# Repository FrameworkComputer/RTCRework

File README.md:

# RTC Rework

## Requesting an RTC Battery Substitute module

If you have an 11th Gen system or Mainboard, you can now [reach out to support](https://framework.kustomer.help/contact/support-request-ryon9uAuq) to request a free RTC Battery Substitute module. 
To make the request process go smoothly, enter the email address that you ordered the 11th Gen product on and/or include photos of the system and Mainboard serial numbers.

Note that there are no constraints making this request other than being an 11th Gen system or Mainboard owner (whether or not you are in warranty), with the exception of those from Mystery Boxes. 
We ask that you really make sure you are comfortable with performing soldering on expensive electronics items before performing the installation, 
as we won’t be able to provide advice or support around soldering or provide fixes for failed soldering attempts. 
We also ask that you only make the request if you’ve faced needing to perform a Mainboard reset, as we want to avoid waste.

## Details

This is a "fake" ML1220 RTC Battery that can be inserted into an 11th Gen Intel Core Framework Laptop Mainboard as a
replacement for a real ML1220.  There is a known issue on 11th Gen where RTC battery voltage dropping below a certain
level can in some scenarios result in the CPU entering a bad state and not booting until the main battery and RTC battery
are cycled.

With this fake RTC Battery, the RTC circuit remains powered from either AC or the main battery at all times,
preventing the CPU from entering the bad state.  Note that since it is not a real battery, if both AC and the main
battery are disconnected, the clock will be reset.  The OS will be able to recover the clock once it connects to a network.
This behavior matches essentially how 12th Gen works with the RTC battery removed, and how 13th Gen and Ryzen 7040 Series work
by default, since we no longer ship with an RTC battery installed.

## Fabrication
The outputs in the outputs directory contain the necessary information to have a fab house like PCBWay or similar fabricate
the PCBs and do SMT and manual assembly.  Note that the PCB must be 2.0mm thick, have ENIG plating, and have edge plating.

## Assembly
Steps 1 through 3 can be done by the PCB fab/assembly supplier (we've used PCBWay, but there are many similar ones), while
the remaining steps are done on the specific Framework Laptop.

1. Strip 3mm from each side of 60mm long, 30 AWG solid wire.
2. Solder one side of the wire to the pad on the top of the PCB that is labelled 17.6V
3. Apply a 10mm diameter disc of kapton tape on the top of the PCB, covering the pad and SMT parts
4. Follow the [step by step guide](https://guides.frame.work/Guide/RTC+Battery+Substitution+on+11th+Gen+Intel%C2%AE+Core%E2%84%A2/203) with photos and video for the remaining steps.

## License
RTC Rework © 2023 by Framework Computer Inc is licensed under CC BY 4.0. To view a copy of this license, visit http://creativecommons.org/licenses/by/4.0/

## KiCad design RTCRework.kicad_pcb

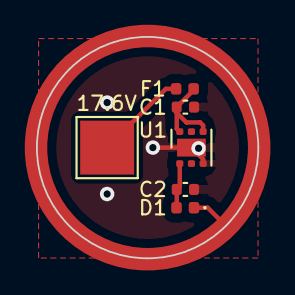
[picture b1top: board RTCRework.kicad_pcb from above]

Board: 2 copper layers, 12.3 x 12.3 mm, 7 parts (1 on the bottom side), 4 nets.

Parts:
C1, C2: 1uF; C_0402_1005Metric
D1: D_Schottky; D_0402_1005Metric
F1: Fuse; Fuse_0402_1005Metric
J1: Conn_01x01; TestPoint_Pad_3.0x3.0mm
J2: Conn_01x01; TestPoint_Pad_D4.0mm
U1: NCP718AMT330TBG; WSON-6-1EP_2x2mm_P0.65mm_EP1x1.6mm

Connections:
+17.6V: F1.1, J1.1
GND: C1.2, C2.2, J2.1, U1.3 (GND), U1.7 (GND)
unnamed: C2.1, D1.2 (A), U1.1 (OUT)
unnamed: C1.1, F1.2, U1.4 (EN), U1.6 (IN)

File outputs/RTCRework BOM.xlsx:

|  |  | xxxx xxxx xxxxx xxPCS BOM (Sample Bill of Materials)
Item # | *Designator | *Qty | Manufacturer | *Mfg Part # | Description / Value | *Package/Footprint | Type | Your Instructions / Notes
1.0 | F1 | 1.0 | Kamaya | FMC10501WHTH | Fuse | 0402 | SMD
2.0 | C1, C2 | 2.0 | Murata | GRM155R6YA105KE11D | 1uF 35V | 0402 | SMD
3.0 | U1 | 1.0 | onsemi | NCP718AMT330TBG | LDO | WSON-6 | SMD
4.0 | D1 | 1.0 | Comchip | CDBQC0130L-HF | Schottky | 0402 | SMD
5.0
6.0
7.0
8.0
9.0
10.0
11.0
12.0
13.0
14.0
15.0

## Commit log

2023-04-11 Remove temporary outputs
2023-04-11 Add fuse, switch to smaller packages
2023-07-06 Update dimensions
2023-07-06 Fabrication outputs
2023-07-06 Update README.md
    Fix images
2023-07-06 Update README.md
    Clarify assembly steps
2023-08-01 Add link to guide
2023-08-09 Add link to support
2025-06-24 Clarify that mystery boxes don't qualify for substitutes
    Mystery boxes don't come with any warranty whatsoever, so the offer mentioned here does not apply. Only to products that originally were bought under warranty.
2025-06-24 Merge pull request #2 from FrameworkComputer/mystery-boxes
    Clarify that mystery boxes don't qualify for substitutes
